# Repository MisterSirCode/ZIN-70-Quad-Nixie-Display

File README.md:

# ZIN-70 Quad Nixie Display
 
### Important Notes

This is a four tube display built using Millclock ZIN-70 Nixie Tubes. This can be used to drive a clock, or just as a numeric display.

Please note that if you decide to use this diaply as a clock, it does not include colons.

### Components and Requirements

Supply:
* Any* 12V 500mA (or better) supply. DC 5.5mm Male Plug

Mechanical and Connectors:
* 1x Same Sky `PJ-063AH` DC 5.5mm Female Connector 
* 1x C&K Switches `DP62J12S202HQ` DPDT Slide Switch (Power Switch)
* 2x Same Sky `TS04-66-85-BK-100-SMT` SPST Button (Hour and Minute buttons)
* 2x Keystone Elec. `1291-66 ` 9V Battery connector

Tubes:
* 4x Millclock `ZIN-70` Nixie Tubes (Z5680M Pinout) - 170V ~5mA each
* 1x NE-2 5mm "Daytime" Indicator (I used a yellow phosphor Mercury/Argon tube)
* 1x NE-2 5mm "Nighttime" Indicator (I used a blue phosphor Mercury/Argon Tube)

Passives:
* 4x 6.8kR 1206(in) SMD Current-Limiting Power Resistors (Nixie Tubes)
* 8x 1kR 1206(in) SMD Current-Limiting Signal Resistors (Outputs)
* 4x 200kR 1206(in) SMD Current-Limiting Power Resistors (Indicator Swapper)
* 2x 100nF 1206(in) SMD Decoupling Capacitors
* 2x 1uF 1206(in) SMD Filter Capacitors
* 2x 10k 1206(in) SMD Filter Resistors

HV Boost Supply:
* 1x Omnixie `NCH8200HV` (12V to 170V 30mA)
    - Custom footprint. Only compatible with NCH8200V.

Driver:
* 1x Murata `OKI-78SR-5/1.5-W36-C` 12-5V DC-DC Converter 
    - Custom footprint for this device. Swap or remove as required
* 1x Murata `OKI-78SR-12/1.0-W36-C` 18-12V DC-DC Converter 
    - Custom footprint for this device. Swap or remove as required
* 1x WaveShare `RP2040-Tiny` devboard 
    - Custom footprint. Please swap for your driver. Only compatible with 23-pin 2.54mm pitch RP2040 tinies.
    - Buy directly from waveshare if you want to avoid incompatibility.

Registers and Chips:
* 1x Texas Instruments `CD40109BPWRE4` TSSOP-16 4bit 3V to 18V Level Converter
    - Configured for 3.3V to 12V conversion specifically for ESP32. Adjust Vcc and Vdd as required.
* 2x Microchip Tech. `HV5122` PQFP-44 32bit HV Registers (220V 100mA Drains)
    - Custom symbol/package configured.

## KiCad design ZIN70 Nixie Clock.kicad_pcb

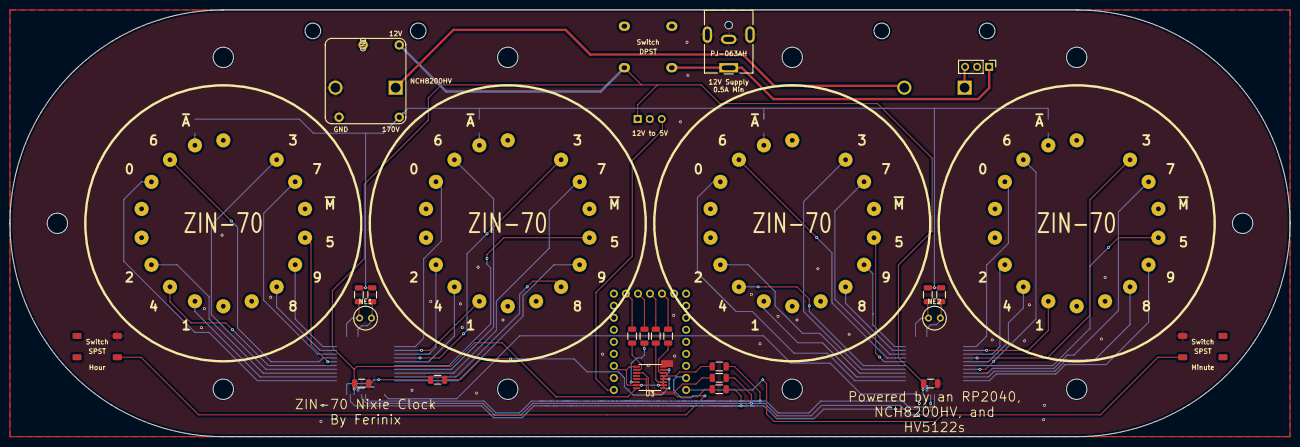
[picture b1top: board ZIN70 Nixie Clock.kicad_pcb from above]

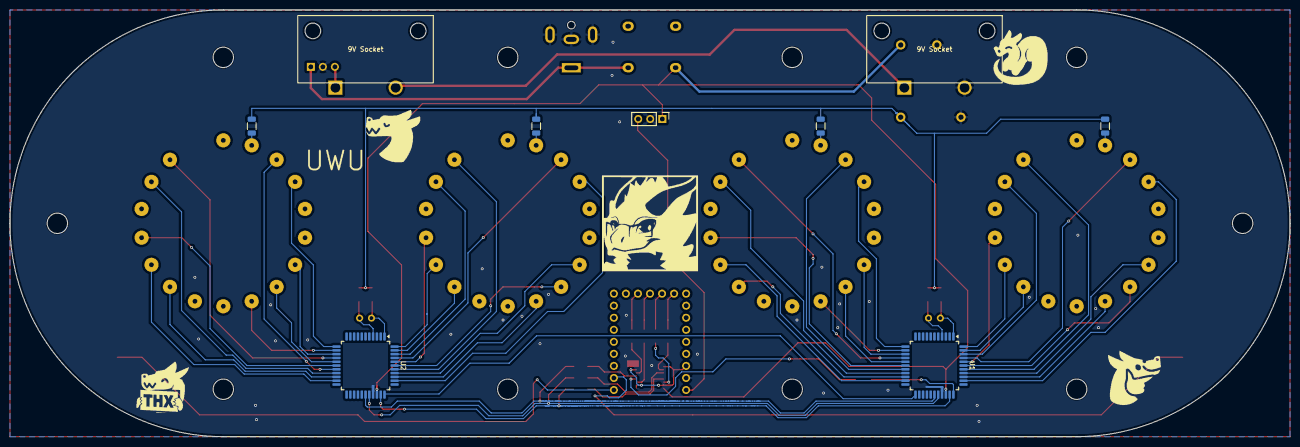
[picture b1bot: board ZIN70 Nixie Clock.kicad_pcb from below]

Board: 2 copper layers, 270.0 x 90.0 mm, 34 parts (8 on the bottom side), 65 nets.

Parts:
9V Socket, 9V Socket#2: 9V Socket Slim
C1, C2: 100nF; C_1206_3216Metric
NCH8200HV: NCH8200HV Through-Hole
NE1, NE2: NE-2; NE-2_5mm
NIX1, NIX2, NIX3, NIX4: ZIN-70; ZIN-70 Z5680M Pinout
PJ-063AH: BarrelJack_CUI_PJ-063AH_Horizontal
R1, R2, R3, R4: 6.8K; R_1206_3216Metric
R5, R6, R7, R8: 200K; R_1206_3216Metric
R9, R10, R11, R12, R13, R14, R15, R16: 1K; R_1206_3216Metric
Switch: TS04-66-85-BK-100-SMT SPST Button
Switch#2: DP62J12S202HQ DPDT Slide Switch
Switch#3: TS04-66-85-BK-100-SMT SPST Button
U1, U2: HV5122; PQFP-44_10x10mm_P0.8mm
U3: CD40109BPW; TSSOP-16_4.4x5mm_P0.65mm

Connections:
+3.3V: U3.1 (V_{CC}), U3.2 (ENABLE_A), U3.7 (ENABLE_B), U3.9 (ENABLE_C), U3.15 (ENABLE_D)
+12V: 9V Socket.2, 9V Socket#2.1, 9V Socket#2.2, C1.1, C2.1, PJ-063AH.1, U1.31 (VDD), U2.31 (VDD), U3.16 (V_{DD})
+170V: R1.1, R2.1, R3.1, R4.1, R5.2, R6.2, R7.2, R8.2
GND: 9V Socket.1, C1.2, C2.2, NCH8200HV.3, NCH8200HV.4, PJ-063AH.2, PJ-063AH.MP, Switch.1, Switch#3.3, U1.30 (GND), U2.30 (GND), U3.8 (V_{SS})
unnamed: NIX1.4 (0), U1.35 (HV1)
unnamed: NIX1.9 (1), U1.36 (HV2)
unnamed: NIX1.7 (2), U1.37 (HV3)
unnamed: NIX1.17 (3), U1.38 (HV4)
unnamed: NIX1.8 (4), U1.39 (HV5)
unnamed: NIX1.14 (5), U1.40 (HV6)
unnamed: NIX1.3 (6), U1.41 (HV7)
unnamed: NIX1.16 (7), U1.42 (HV8)
unnamed: NIX1.12 (8), U1.43 (HV9)
unnamed: NIX1.13 (9), U1.44 (HV10)
unnamed: NIX1.2 (~A), R1.2
unnamed: NIX2.4 (0), U1.12 (HV22)
unnamed: NIX2.9 (1), U1.13 (HV23)
unnamed: NIX2.7 (2), U1.14 (HV24)
unnamed: NIX2.17 (3), U1.15 (HV25)
unnamed: NIX2.8 (4), U1.16 (HV26)
unnamed: NIX2.14 (5), U1.17 (HV27)
unnamed: NIX2.3 (6), U1.18 (HV28)
unnamed: NIX2.16 (7), U1.19 (HV29)
unnamed: NIX2.12 (8), U1.20 (HV30)
unnamed: NIX2.13 (9), U1.21 (HV31)
unnamed: NIX2.2 (~A), R2.2
unnamed: NIX3.4 (0), U2.35 (HV1)
unnamed: NIX3.9 (1), U2.36 (HV2)
unnamed: NIX3.7 (2), U2.37 (HV3)
unnamed: NIX3.17 (3), U2.38 (HV4)
unnamed: NIX3.8 (4), U2.39 (HV5)
unnamed: NIX3.14 (5), U2.40 (HV6)
unnamed: NIX3.3 (6), U2.41 (HV7)
unnamed: NIX3.16 (7), U2.42 (HV8)
unnamed: NIX3.12 (8), U2.43 (HV9)
unnamed: NIX3.13 (9), U2.44 (HV10)
unnamed: NIX3.2 (~A), R3.2
unnamed: NIX4.4 (0), U2.12 (HV22)
unnamed: NIX4.9 (1), U2.13 (HV23)
unnamed: NIX4.7 (2), U2.14 (HV24)
unnamed: NIX4.17 (3), U2.15 (HV25)
unnamed: NIX4.8 (4), U2.16 (HV26)
unnamed: NIX4.14 (5), U2.17 (HV27)
unnamed: NIX4.3 (6), U2.18 (HV28)
unnamed: NIX4.16 (7), U2.19 (HV29)
unnamed: NIX4.12 (8), U2.20 (HV30)
unnamed: NIX4.13 (9), U2.21 (HV31)
unnamed: NIX4.2 (~A), R4.2
unnamed: R10.1, U1.29 (CLK), U2.29 (CLK)
unnamed: U1.23 (DATAOUT), U2.33 (DIN)
unnamed: R12.1, U1.33 (DIN)
unnamed: R5.1, U1.1 (HV11)
unnamed: R6.1, U1.4 (HV14)
unnamed: R9.1, U1.32 (STR), U2.32 (STR)
unnamed: R11.1, U1.28 (~OE), U2.28 (~OE)
unnamed: R7.1, U2.1 (HV11)
unnamed: R8.1, U2.4 (HV14)
unnamed: R13.1, U3.3 (A)
unnamed: R14.1, U3.6 (B)
unnamed: R15.1, U3.10 (C)
unnamed: R16.1, U3.14 (D)
unnamed: R12.2, U3.4 (E)
unnamed: R11.2, U3.5 (F)
unnamed: R10.2, U3.11 (G)
unnamed: R9.2, U3.13 (H)

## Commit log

2026-02-16 Add files
2026-02-16 Add readme information
2026-02-16 Minor configuration
2026-02-20 Update the clock with 5mm indicators
2026-02-20 Adjustments
2026-02-23 Major changes to design
2026-02-23 Add new parts and changes to the readme
2026-02-23 Silly temp issue
2026-02-23 Forgot to include indicators
2026-02-25 Add debounce RC filters
2026-02-27 Last minute changes before printing
